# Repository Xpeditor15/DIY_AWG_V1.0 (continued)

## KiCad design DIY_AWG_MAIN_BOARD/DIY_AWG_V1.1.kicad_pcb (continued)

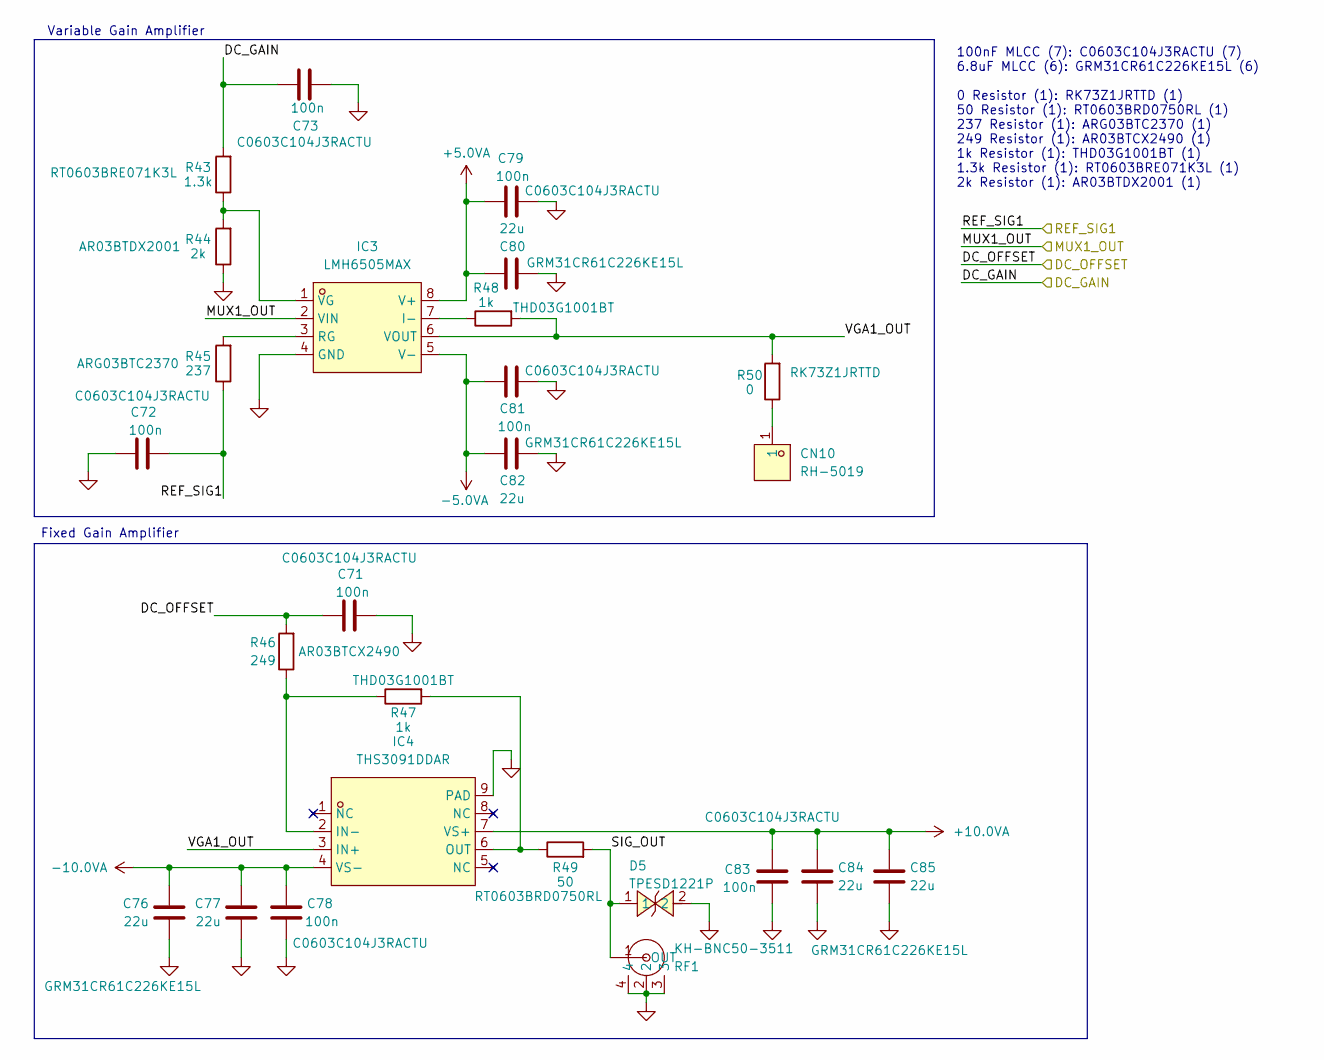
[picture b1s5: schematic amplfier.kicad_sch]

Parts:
C71, C72, C73, C78, C79, C81, C83: 100n; C_0603_1608Metric; LCSC ID C2167388
C76, C77, C80, C82, C84, C85: 22u; C_1206_3216Metric; LCSC ID C77088
CN10: RH-5019; TESTPOINT-SMD_L3.8-W2.0_RH-5019; MPN RH-5019; LCSC Part C5199800
D5: TPESD1221P; DFN1006-2L-BI; MPN TPESD1221P; LCSC Part C521899
IC3: LMH6505MAX; SOP-8_L4.9-W3.9-P1.27-LS6.0-BL; Manufacturer_Part_Number LMH6505MAX; LCSC Part C2060587
IC4: THS3091DDAR; SOIC-8_L4.9-W3.9-P1.27-LS6.0-BL-EP; Manufacturer_Part_Number THS3091DDAR; Mouser Part Number 595-THS3091DDAR
R43: 1.3k; R_0603_1608Metric; LCSC ID C136957
R44: 2k; R_0603_1608Metric; LCSC ID C319701
R45: 237; R_0603_1608Metric; LCSC ID C2681612
R46: 249; R_0603_1608Metric; LCSC ID C2984337
R47, R48: 1k; R_0603_1608Metric; LCSC ID C52104281
R49: 50; R_0603_1608Metric; LCSC ID C5879483
R50: 0; R_0603_1608Metric; LCSC ID C2596815
RF1: KH-BNC50-3511; ANT-TH_KH-BNC50-3511; MPN KH-BNC50-3511; LCSC Part C2837587

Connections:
+5.0VA: C79.2, C80.2, IC3.8 (V+); also elsewhere on the board
+10.0VA: C83.1, C84.1, C85.1, IC4.7 (VS+); also elsewhere on the board
-5.0VA: C81.2, C82.2, IC3.5 (V-); also elsewhere on the board
-10.0VA: C76.1, C77.1, C78.1, IC4.4 (VS-); also elsewhere on the board
/AD9834_DDS/DC_GAIN: C73.1, R43.2; also elsewhere on the board
/AD9834_DDS/DC_OFFSET: C71.1, R46.2; also elsewhere on the board
/AD9834_DDS/MUX1_OUT: IC3.2 (VIN); also elsewhere on the board
/AD9834_DDS/REF_SIG1: C72.2, R45.1; also elsewhere on the board
/Amplifier/SIG_OUT: D5.1, R49.2, RF1.1 (OUT)
/Amplifier/VGA1_OUT: IC3.6 (VOUT), IC4.3 (IN+), R48.2, R50.2
GND: C71.2, C72.1, C73.2, C76.2, C77.2, C78.2, C79.1, C80.1, C81.1, C82.1, C83.2, C84.2, C85.2, D5.2, IC3.4 (GND), IC4.9 (PAD), R44.1, RF1.2, RF1.3, RF1.4; also elsewhere on the board
unnamed: CN10.1 (1_1), R50.1
unnamed: IC3.7 (I-), R48.1
unnamed: IC3.3 (RG), R45.2
unnamed: IC3.1 (VG), R43.1, R44.2
unnamed: IC4.2 (IN-), R46.1, R47.1
unnamed: IC4.6 (OUT), R47.2, R49.1

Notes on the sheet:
Variable Gain Amplifier
Fixed Gain Amplifier
100nF MLCC (7): C0603C104J3RACTU (7) 6.8uF MLCC (6): GRM31CR61C226KE15L (6) 0 Resistor (1): RK73Z1JRTTD (1) 50 Resistor (1): RT0603BRD0750RL (1) 237 Resistor (1): ARG03BTC2370 (1) 249 Resistor (1): AR03BTCX2490 (1) 1k Resistor (1): THD03G1001BT (1) 1.3k Resistor (1): RT0603BRE071K3L (1) 2k Resistor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

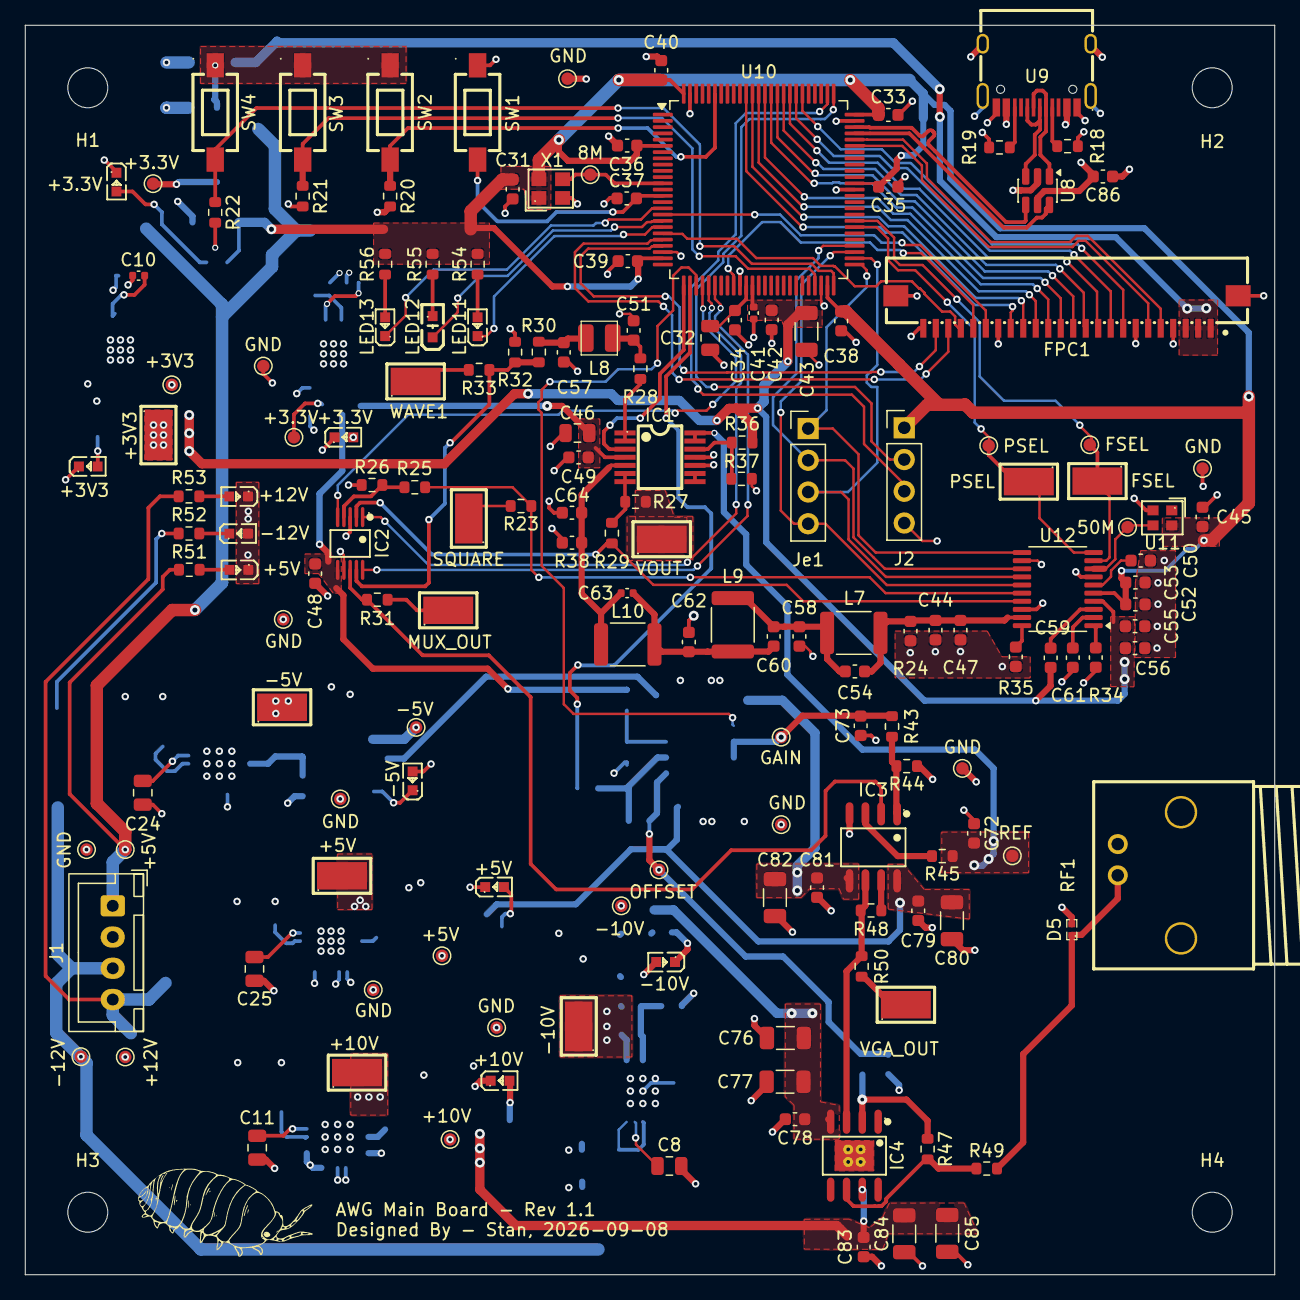
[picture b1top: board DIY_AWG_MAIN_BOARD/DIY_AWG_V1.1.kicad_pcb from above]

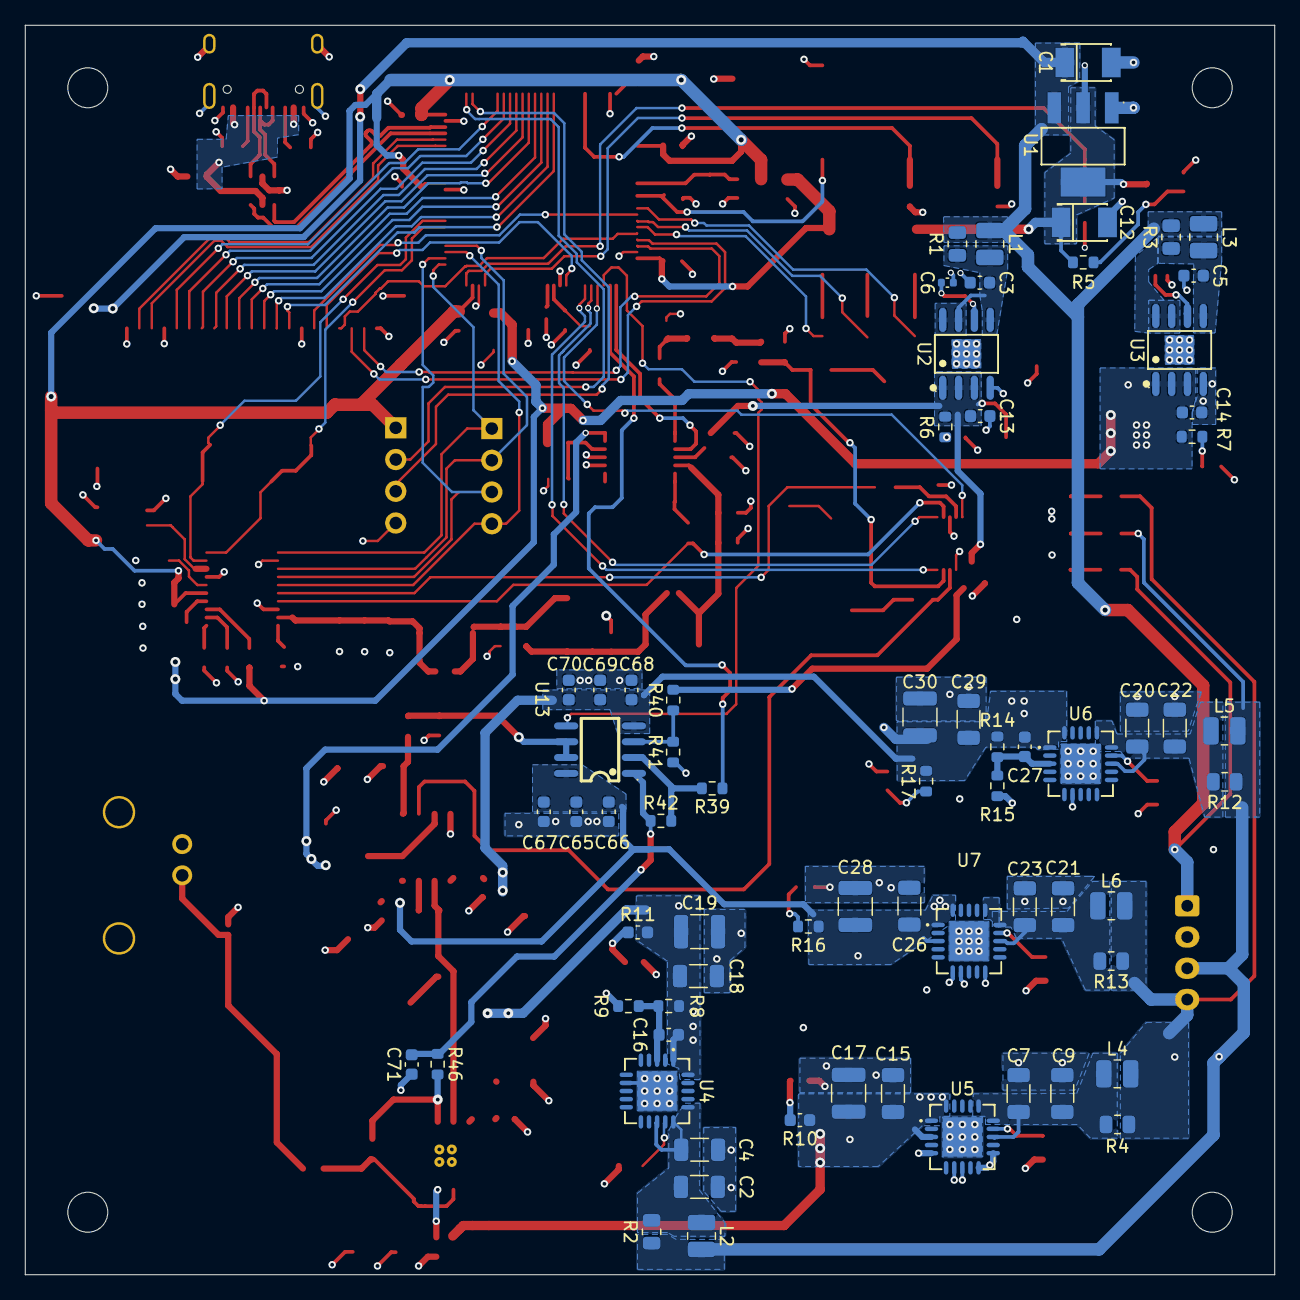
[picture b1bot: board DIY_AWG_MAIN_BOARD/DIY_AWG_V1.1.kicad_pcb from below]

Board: 4 copper layers, 100.0 x 100.0 mm, 234 parts (68 on the bottom side), 123 nets.

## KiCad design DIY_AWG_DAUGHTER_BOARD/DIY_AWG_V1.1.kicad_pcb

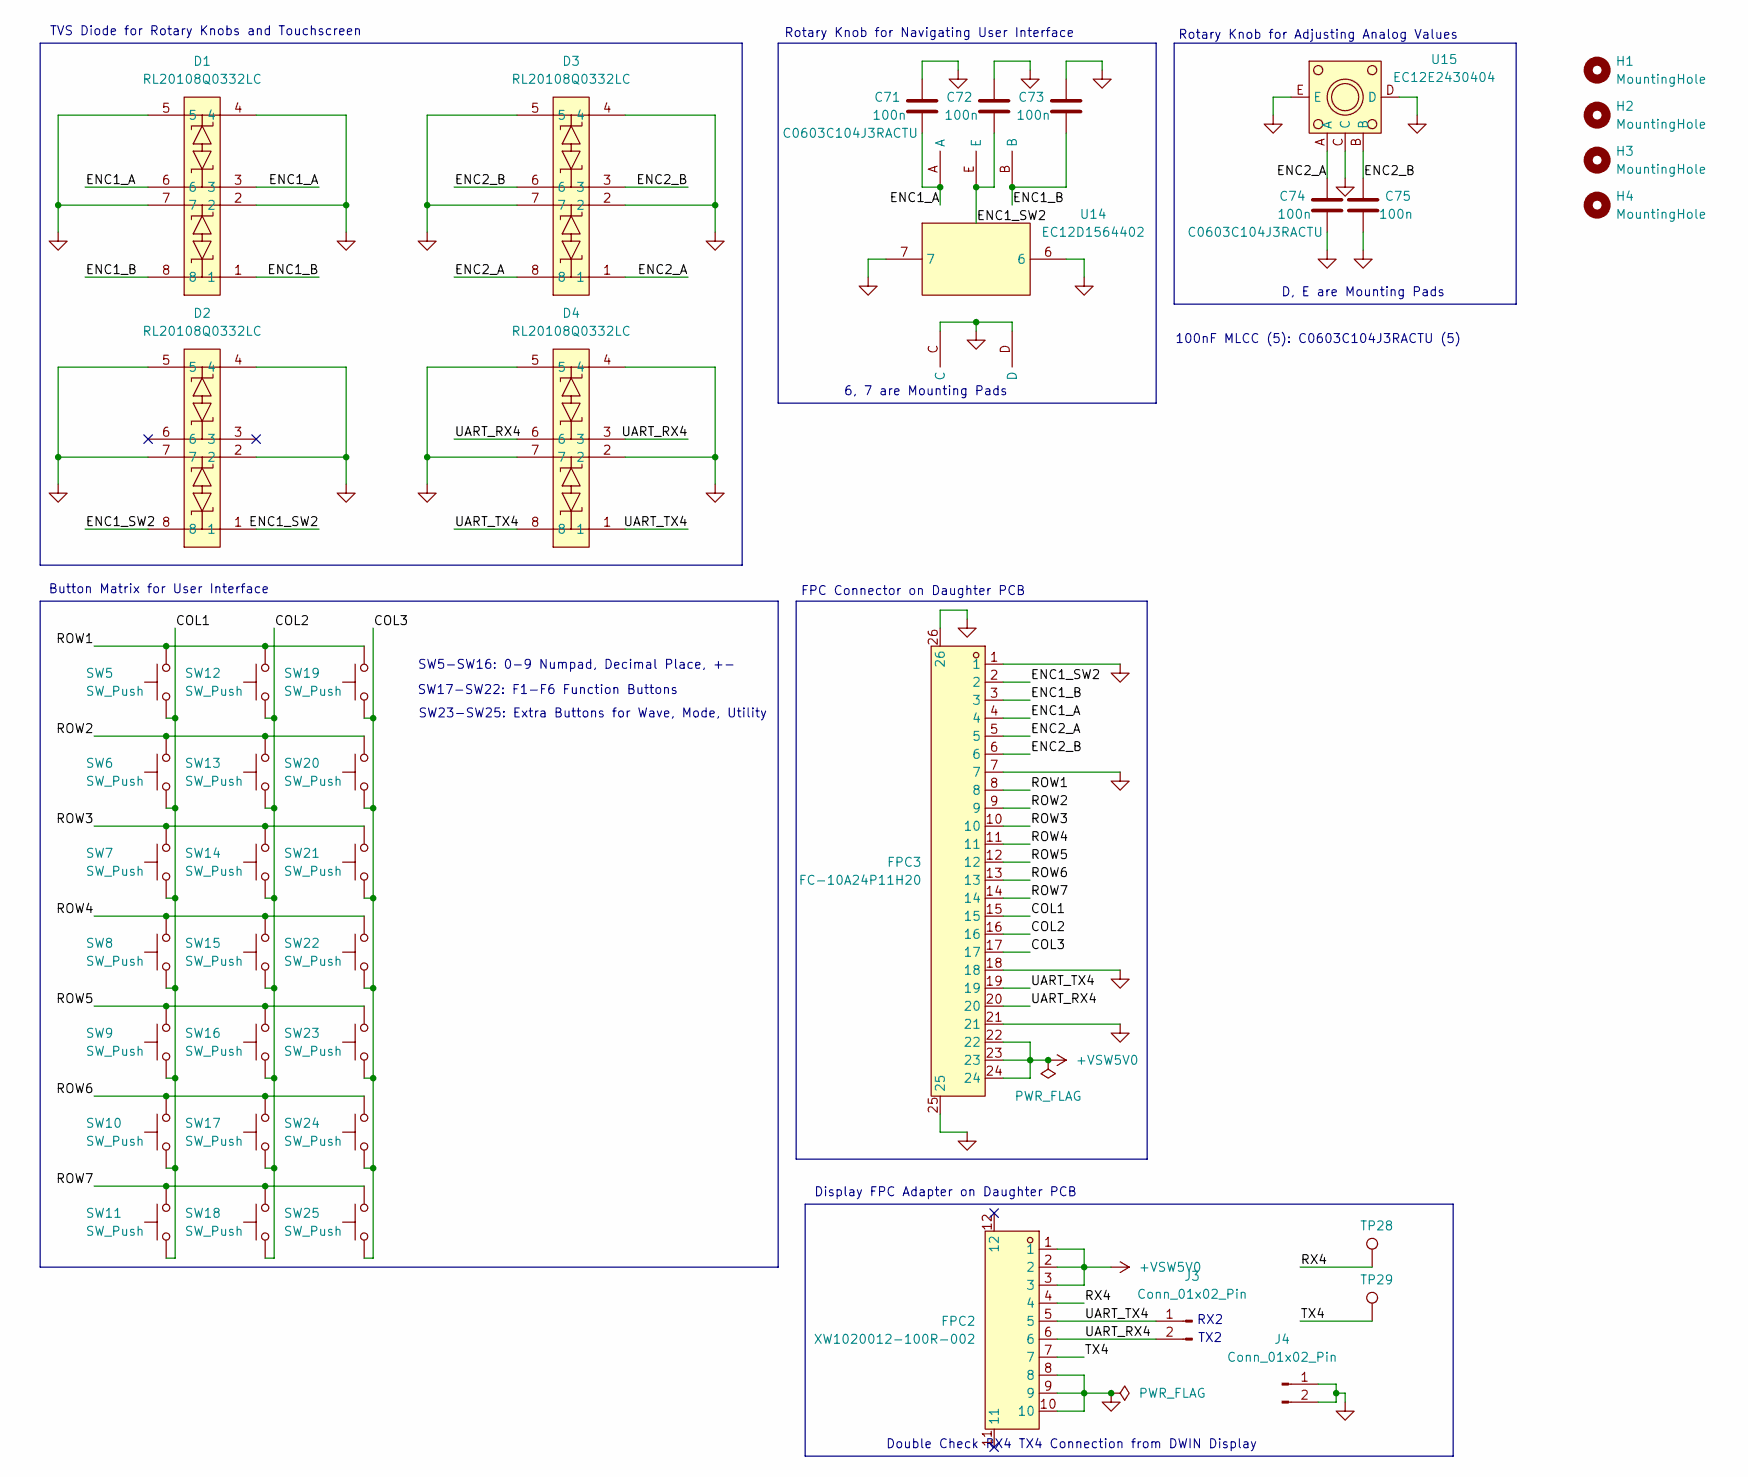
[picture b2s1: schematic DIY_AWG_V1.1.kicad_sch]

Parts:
C71, C72, C73, C74, C75: 100n; C_0603_1608Metric; LCSC ID C2167388
D1, D2, D3, D4: RL20108Q0332LC; DFN-8_L2.0-W1.0-P0.50-BL; MPN RL20108Q0332LC; LCSC Part C46970962
FPC2: XW1020012-100R-002; FPC-SMD_10P-P1.00_XW1020012-100R-001; MPN XW1020012-100R-002; LCSC Part C41416813
FPC3: FC-10A24P11H20; FPC-SMD_24P-P1.00_FC-10A24P11H20; MPN FC-10A24P11H20; LCSC Part C23397378
H1, H2, H3, H4: MountingHole; MountingHole_3.2mm_M3
J3, J4: Conn_01x02_Pin; PinHeader_1x02_P2.54mm_Vertical
SW5, SW6, SW7, SW8, SW9, SW10, SW11, SW12, SW13, SW14, SW15, SW16, SW17, SW18, SW19, SW20, SW21, SW22, SW23, SW24, SW25: SW_Push; SW-SMD_L6.1-W3.5-LS8.6
TP28, TP29: TestPoint; TestPoint_Pad_D1.0mm
U14: EC12D1564402; SW-TH_EC12D1564402; Manufacturer_Part_Number EC12D1564402; Mouser Part Number 688-EC12D1564402
U15: EC12E2430404; SW-TH_ALPSALPINE_EC12EXXXX; Manufacturer_Part_Number EC12E2430404; Mouser Part Number 688-EC12E2430404

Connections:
+VSW5V0: FPC2.1, FPC2.2, FPC2.3, FPC3.22, FPC3.23, FPC3.24
/COL1: FPC3.15, SW5.1, SW6.1, SW7.1, SW8.1, SW9.1, SW10.1, SW11.1
/COL2: FPC3.16, SW12.1, SW13.1, SW14.1, SW15.1, SW16.1, SW17.1, SW18.1
/COL3: FPC3.17, SW19.1, SW20.1, SW21.1, SW22.1, SW23.1, SW24.1, SW25.1
/ENC1_A: C71.1, D1.3, D1.6, FPC3.4, U14.A
/ENC1_B: C73.1, D1.1, D1.8, FPC3.3, U14.B
/ENC1_SW2: C72.1, D2.1, D2.8, FPC3.2, U14.E
/ENC2_A: C74.2, D3.1, D3.8, FPC3.5, U15.A
/ENC2_B: C75.2, D3.3, D3.6, FPC3.6, U15.B
/ROW1: FPC3.8, SW5.2, SW12.2, SW19.2
/ROW2: FPC3.9, SW6.2, SW13.2, SW20.2
/ROW3: FPC3.10, SW7.2, SW14.2, SW21.2
/ROW4: FPC3.11, SW8.2, SW15.2, SW22.2
/ROW5: FPC3.12, SW9.2, SW16.2, SW23.2
/ROW6: FPC3.13, SW10.2, SW17.2, SW24.2
/ROW7: FPC3.14, SW11.2, SW18.2, SW25.2
/RX4: FPC2.4, TP28.1 (1_1)
/TX4: FPC2.7, TP29.1 (1_1)
/UART_RX4: D4.3, D4.6, FPC2.6, FPC3.20, J3.2
/UART_TX4: D4.1, D4.8, FPC2.5, FPC3.19, J3.1
GND: C71.2, C72.2, C73.2, C74.1, C75.1, D1.2, D1.4, D1.5, D1.7, D2.2, D2.4, D2.5, D2.7, D3.2, D3.4, D3.5, D3.7, D4.2, D4.4, D4.5, D4.7, FPC2.8, FPC2.9, FPC2.10, FPC3.1, FPC3.7, FPC3.18, FPC3.21, FPC3.25, FPC3.26, J4.1, J4.2, U14.6, U14.7, U14.C, U14.D, U15.C, U15.D, U15.E

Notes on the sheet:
SW17-SW22: F1-F6 Function Buttons
SW23-SW25: Extra Buttons for Wave, Mode, Utility
Double Check RX4 TX4 Connection from DWIN Display
100nF MLCC (5): C0603C104J3RACTU (5)
Display FPC Adapter on Daughter PCB
Button Matrix for User Interface
RX2
6, 7 are Mounting Pads
Rotary Knob for Adjusting Analog Values
FPC Connector on Daughter PCB
TVS Diode for Rotary Knobs and Touchscreen
TX2
SW5-SW16: 0-9 Numpad, Decimal Place, +-
D, E are Mounting Pads
Rotary Knob for Navigating User Interface

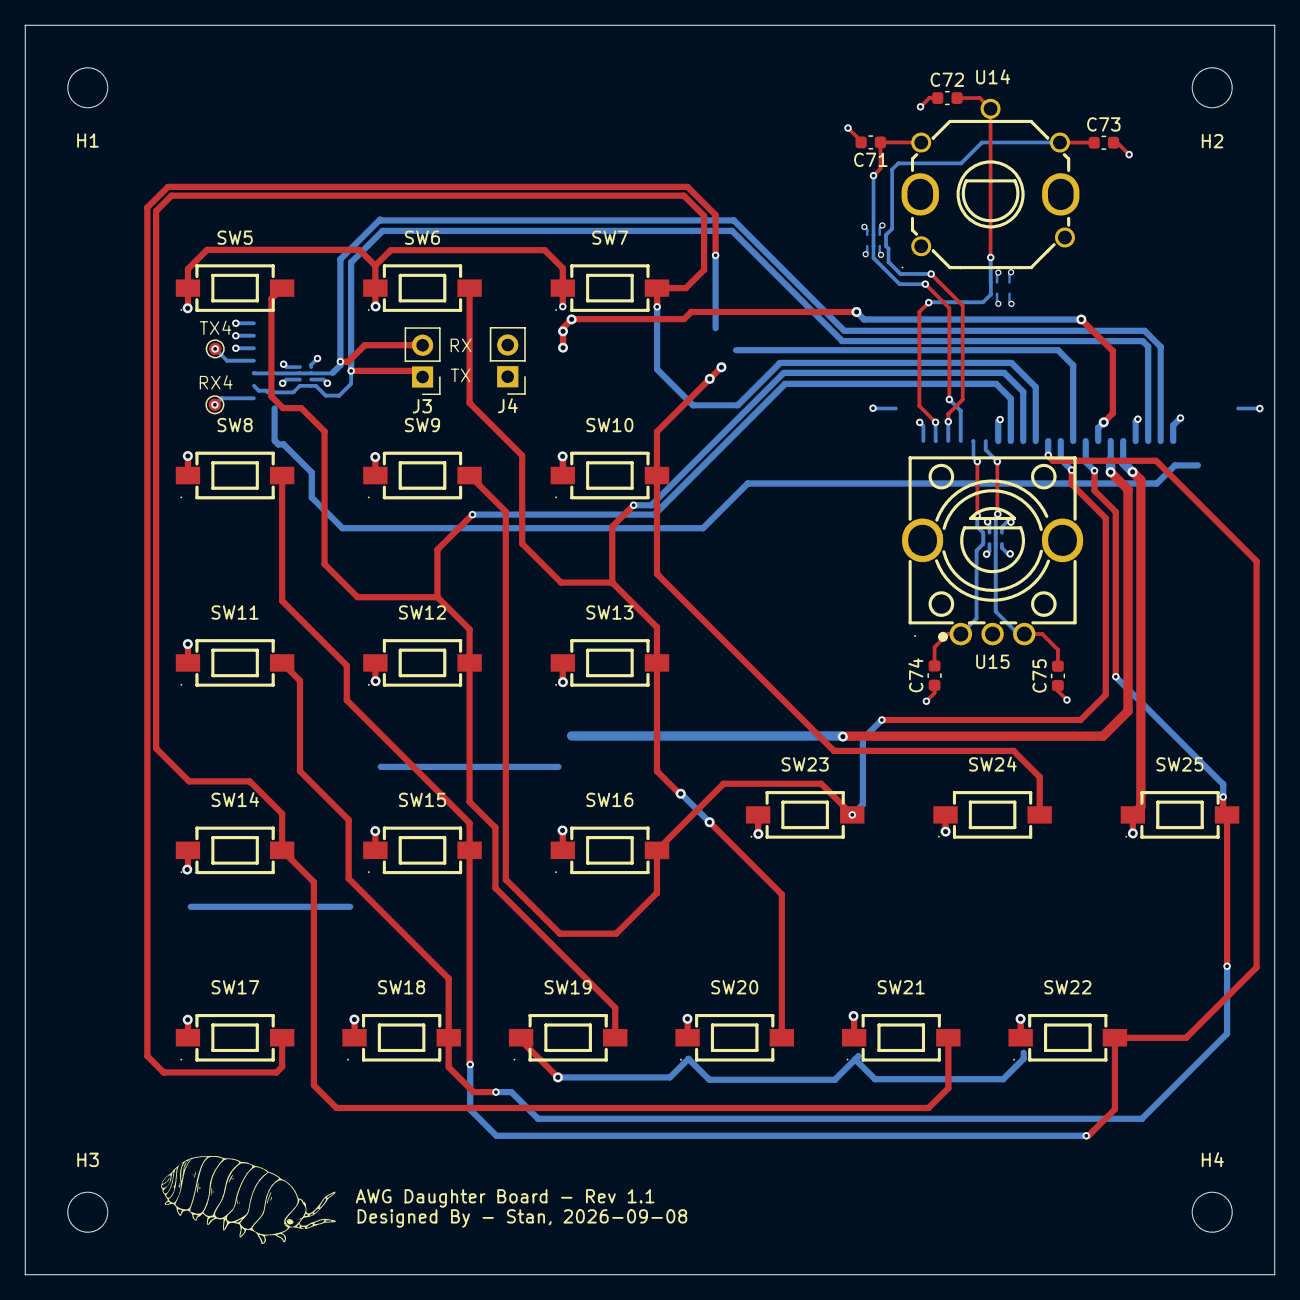
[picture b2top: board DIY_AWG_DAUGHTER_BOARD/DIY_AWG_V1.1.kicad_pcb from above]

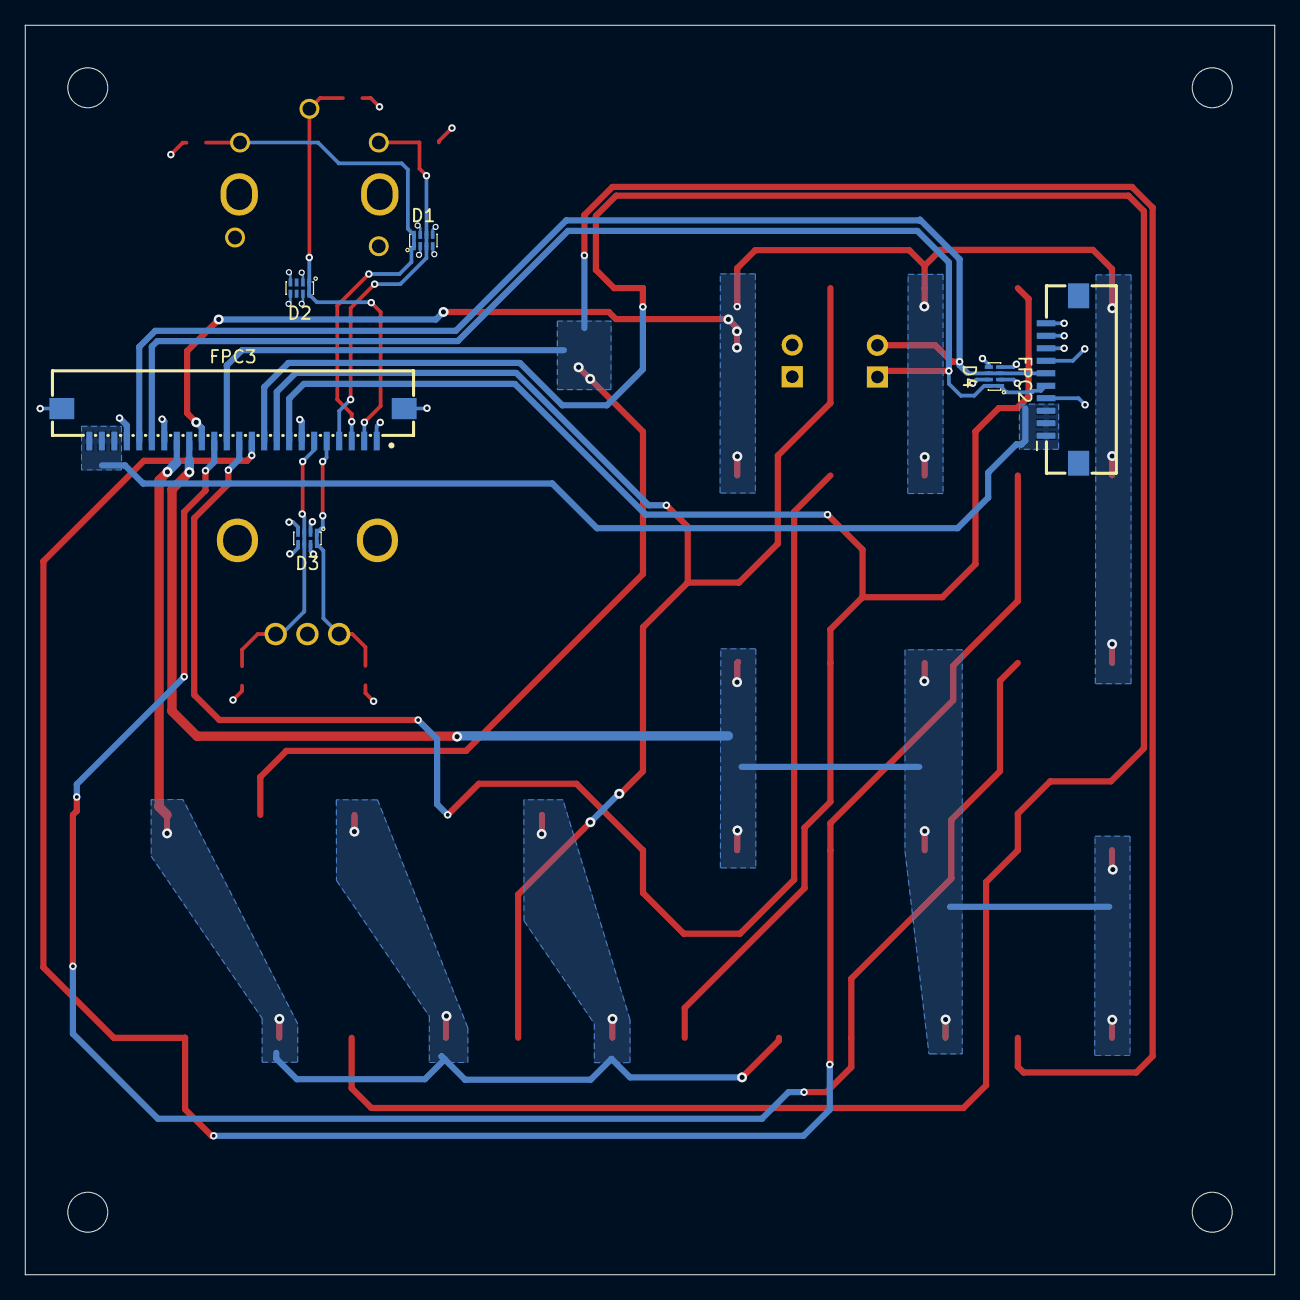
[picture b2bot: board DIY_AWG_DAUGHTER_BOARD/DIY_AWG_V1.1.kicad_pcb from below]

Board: 4 copper layers, 100.0 x 100.0 mm, 42 parts (6 on the bottom side), 21 nets.
